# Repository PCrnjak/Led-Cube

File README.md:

# **Led-Cube**

## Intro

Small and compact led cube powered by usb  that is (kinda) easy to build.I decided to make this project for my own amusement and to train smd soldering and pcb design. Code and program are not made  by me all credit goes to: http://www.instructables.com/id/LED-CUBE-CODE-4x4x4-Arduino/ .

## Table of contents
 1. [Intro](#intro)
 2. [Table of contents](#table)
 3. [Bill of materials](#bill)
 4. [Making boards](#board)
 5. [Soldering components](#solder)
 6. [Burning Arduino bootloader](#burn)
 7. [Code](#code)
 8. [Case](#case)

## Bill of materials
  [ Bill of materials](https://github.com/Ropecar5/Led-Cube/blob/master/BILL%20OF%20MATERIALS.txt)
# Making boards
in [GBRLS](https://github.com/Ropecar5/Led-Cube/tree/master/GRBLS) folder there are all grbl files needed to make boards for led cube.
you will need to make 2 boards ,one top one on wich you will place your led cube and one bottom one that has all electronics.
There are also Eagle schematic and board files for both pcbs . I ordered them [JLC pcb](https://jlcpcb.com/) and they came fine.

# Soldering components
 Well you will need to have some skills with soldering iron and solder all those smd components. Hardest part is soldering leds .You will need to cut 16 3mm holes that are 1.5 mm one from another on peace of cardboard. This will keep all leds at exact distance and make soldering easier.you will need to solder all 4 led planes with magnet wire to pcb board.
 
 # Burning Arduino bootlaoder
 Maybe you can find those smd atmega 328 with already burnt bootloader or you can burn it yourself. I made a mistake on board and didnt want to redo it so to burn bootloader follow these instructions.
 solder wires like shown in picture ,  and connect them to ftdi programmer .
Miso to miso , mosi to mosi , sck to sck , gnd to gnd ,vcc to vcc,DTR ON LED BOARD is not dtr .
Connect dtr from ftdi programmer to wire that is shown on picture.Cap on picture is 47 uF.

# Code
Once again code is not written by me. There are 2 example programs [LEDFADE](https://github.com/Ropecar5/Led-Cube/tree/master/LEDFADE) and
[shooting star](https://github.com/Ropecar5/Led-Cube/tree/master/shooting_star).[LCCG.exe](https://github.com/Ropecar5/Led-Cube/blob/master/LCCG.exe) is program used to generate patterns in wich cube will light up.  To upload code you will need FTDI usb to TTL serial converter that connects to corresponding pins on board.
# Case
[STL](https://github.com/Ropecar5/Led-Cube/tree/master/files) file. Printed on cheap chinese prusa clone with 0.2 mm layer height.

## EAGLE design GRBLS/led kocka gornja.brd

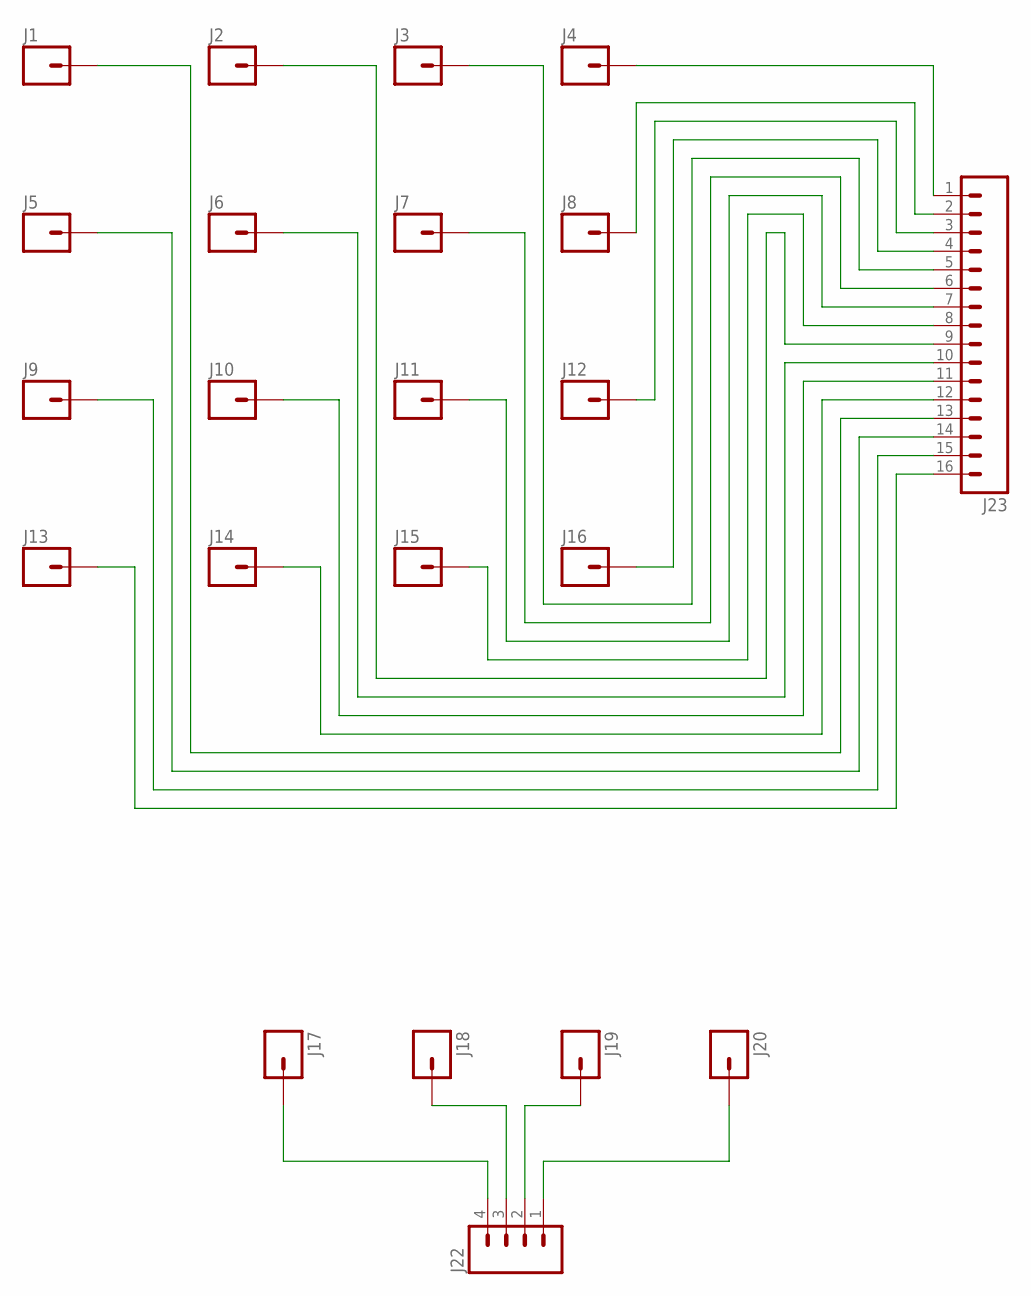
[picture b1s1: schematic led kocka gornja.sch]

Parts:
J1, J2, J3, J4, J5, J6, J7, J8, J9, J10, J11, J12, J13, J14, J15, J16, J17, J18, J19, J20: M01NOSILK-KIT; 1X01NS-KIT
J22: M04LONGPADS; 1X04_LONGPADS
J23: M16LONGPADS; 1X16_LONGPADS

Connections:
unnamed: J4.1, J23.1
unnamed: J8.1, J23.2
unnamed: J12.1, J23.3
unnamed: J16.1, J23.4
unnamed: J3.1, J23.5
unnamed: J7.1, J23.6
unnamed: J11.1, J23.7
unnamed: J15.1, J23.8
unnamed: J2.1, J23.9
unnamed: J6.1, J23.10
unnamed: J14.1, J23.12
unnamed: J1.1, J23.13
unnamed: J10.1, J23.11
unnamed: J5.1, J23.14
unnamed: J9.1, J23.15
unnamed: J13.1, J23.16
unnamed: J17.1, J22.4
unnamed: J20.1, J22.1
unnamed: J18.1, J22.3
unnamed: J19.1, J22.2

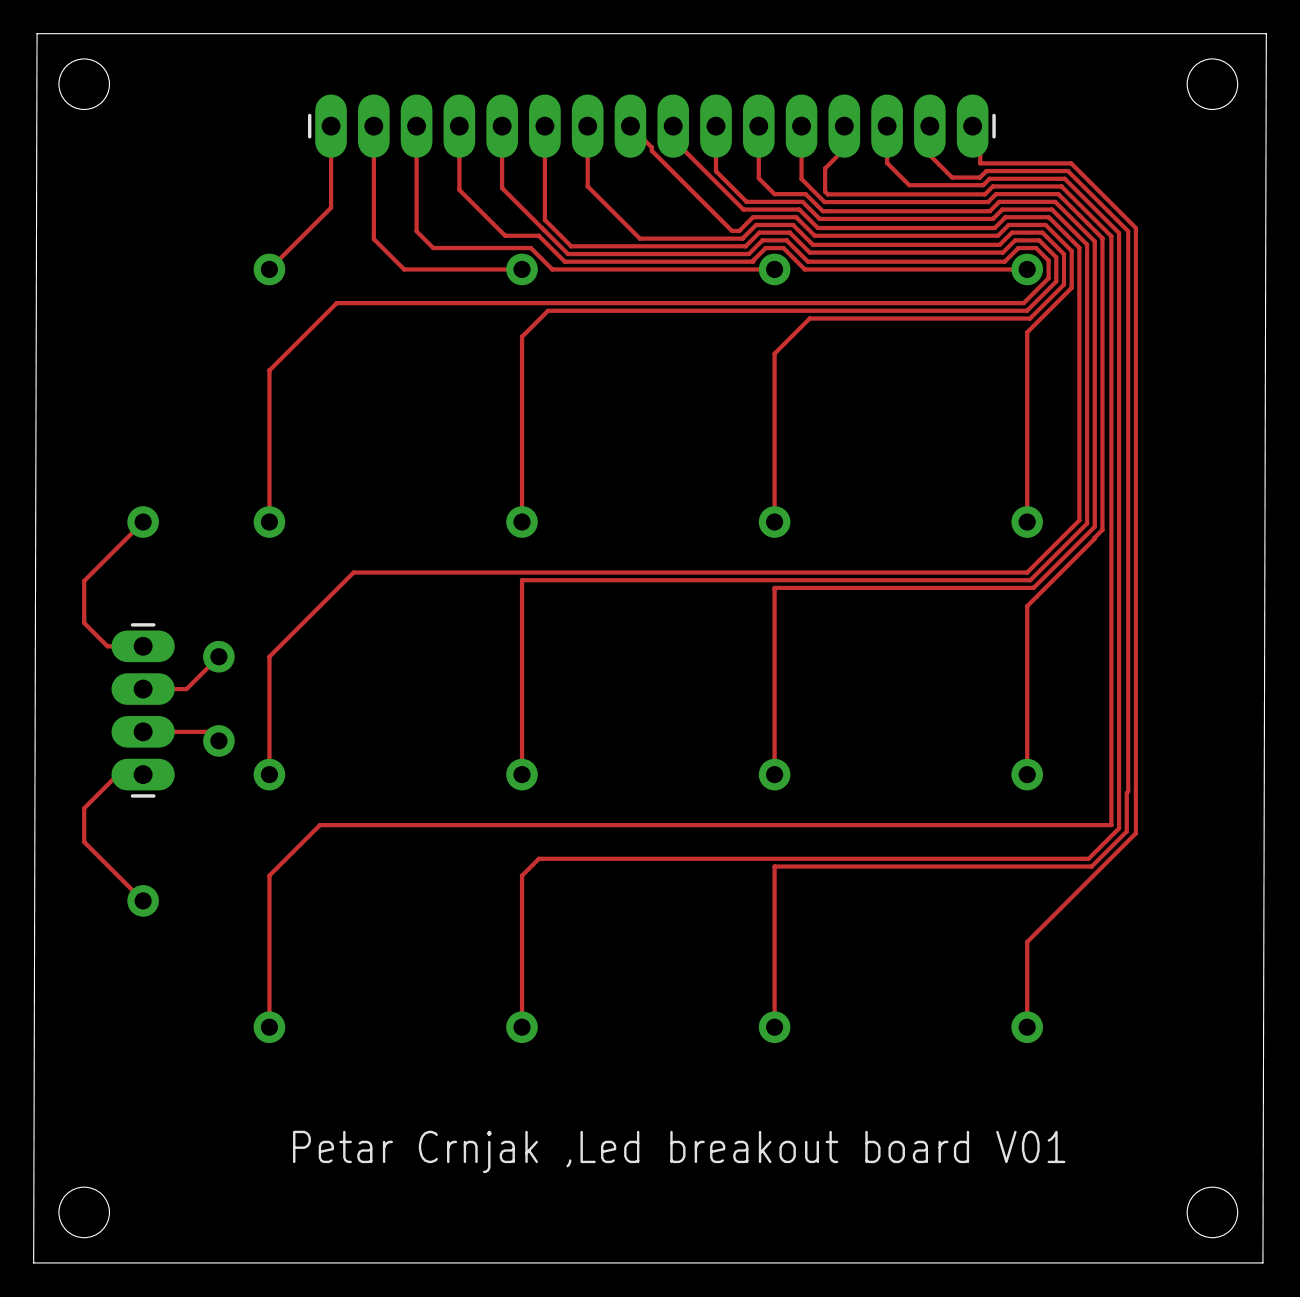
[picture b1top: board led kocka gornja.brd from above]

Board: 2 copper layers, 73.2 x 73.0 mm, 22 parts (0 on the bottom side), 20 nets.

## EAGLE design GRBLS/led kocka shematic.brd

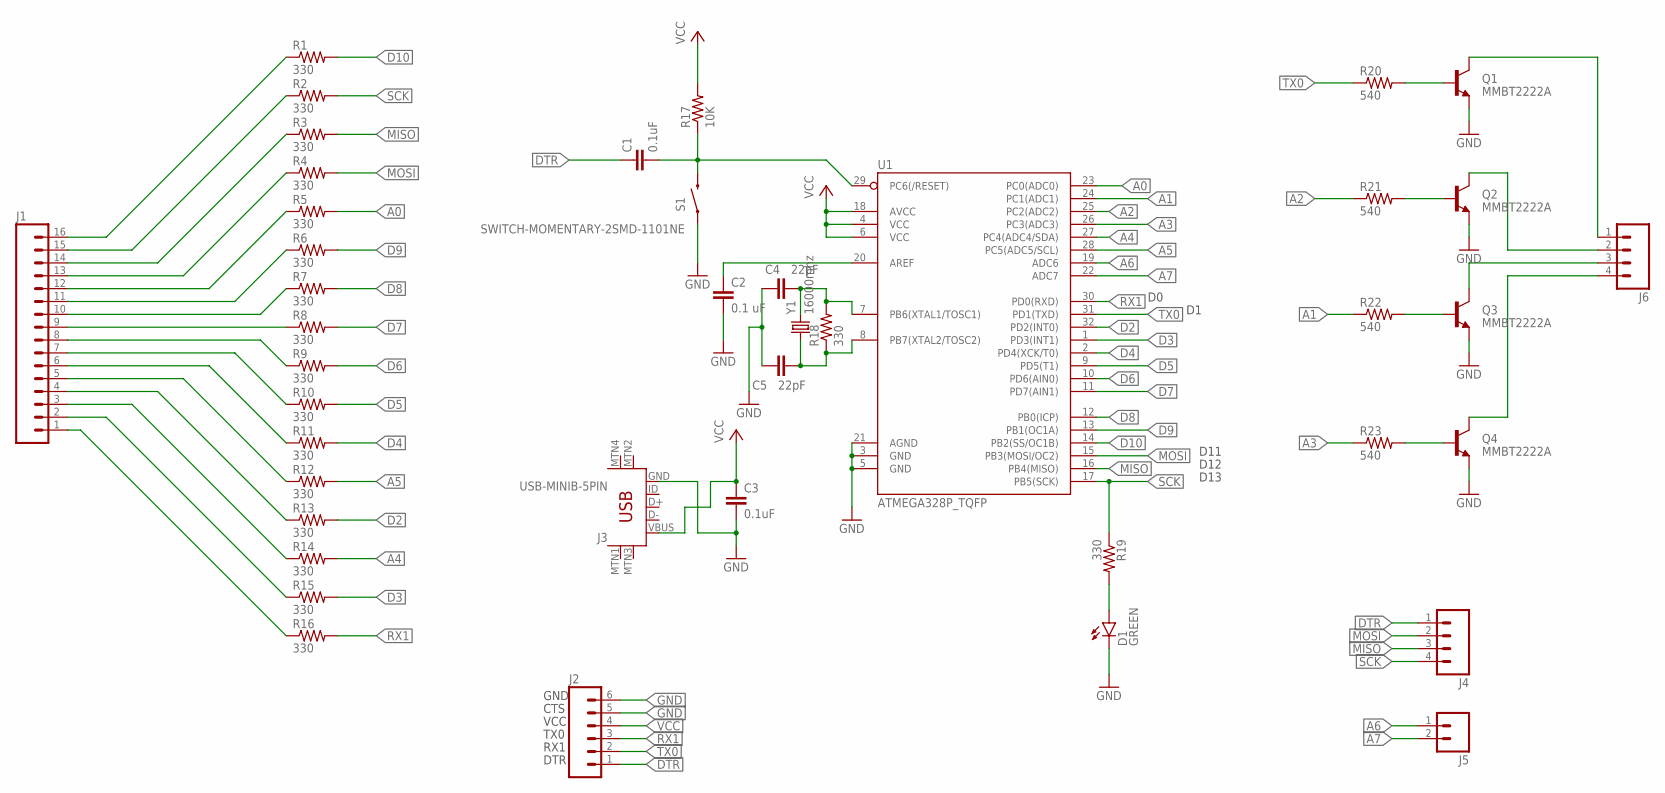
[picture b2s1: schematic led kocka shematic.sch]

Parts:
C1, C3: 0.1uF; 0805-CAP
C2: 0.1 uF; 0805-CAP
C4, C5: 22pF; 0805-CAP
D1: GREEN; LED-0603
J1: M16LONGPADS; 1X16_LONGPADS
J2: M06LONGPADS; 1X06_LONGPADS
J3: USB-MINIB-5PIN; USB-MINIB
J4, J6: M04LONGPADS; 1X04_LONGPADS
J5: M02LOCK_LONGPADS; 1X02_LOCK_LONGPADS
Q1, Q2, Q3, Q4: MMBT2222A; SOT23-3
R1, R2, R3, R4, R5, R6, R7, R8, R9, R10, R11, R12, R13, R14, R15, R16, R18, R19: 330; R0805
R17: 10K; R0805
R20, R21, R22, R23: 540; R0805
S1: SWITCH-MOMENTARY-2SMD-1101NE; TACTILE-SWITCH-1101NE
U1: ATMEGA328P_TQFP; TQFP32-08
Y1: 16000mhz; HC49UP

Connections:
A0: R5.2, U1.23 (PC0(ADC0))
A1: R22.1, U1.24 (PC1(ADC1))
A2: R21.1, U1.25 (PC2(ADC2))
A3: R23.1, U1.26 (PC3(ADC3))
A4: R14.2, U1.27 (PC4(ADC4/SDA))
A5: R12.2, U1.28 (PC5(ADC5/SCL))
A6: J5.1, U1.19 (ADC6)
A7: J5.2, U1.22 (ADC7)
D2: R13.2, U1.32 (PD2(INT0))
D3: R15.2, U1.1 (PD3(INT1))
D4: R11.2, U1.2 (PD4(XCK/T0))
D5: R10.2, U1.9 (PD5(T1))
D6: R9.2, U1.10 (PD6(AIN0))
D7: R8.2, U1.11 (PD7(AIN1))
D8: R7.2, U1.12 (PB0(ICP))
D9: R6.2, U1.13 (PB1(OC1A))
D10: R1.2, U1.14 (PB2(SS/OC1B))
DTR: C1.1, J2.1, J4.1
GND: C2.2, C3.2, C4.1, C5.1, D1.C, J2.5, J2.6, J3.GND, Q1.2 (E), Q2.2 (E), Q3.2 (E), Q4.2 (E), S1.1, U1.3 (GND), U1.5 (GND), U1.21 (AGND)
MISO: J4.3, R3.2, U1.16 (PB4(MISO))
MOSI: J4.2, R4.2, U1.15 (PB3(MOSI/OC2))
unnamed: C4.2, R18.2, U1.7 (PB6(XTAL1/TOSC1)), Y1.2
unnamed: J1.16, R1.1
unnamed: C1.2, R17.1, S1.2, U1.29 (PC6(/RESET))
unnamed: C5.2, R18.1, U1.8 (PB7(XTAL2/TOSC2)), Y1.1
unnamed: C2.1, U1.20 (AREF)
unnamed: J1.15, R2.1
unnamed: J1.14, R3.1
unnamed: J1.13, R4.1
unnamed: J1.12, R5.1
unnamed: J1.11, R6.1
unnamed: D1.A, R19.2
unnamed: J1.1, R16.1
unnamed: J1.2, R15.1
unnamed: J1.3, R14.1
unnamed: J1.4, R13.1
unnamed: J1.5, R12.1
unnamed: J1.6, R11.1
unnamed: J1.7, R10.1
unnamed: J1.8, R9.1
unnamed: J1.9, R8.1
unnamed: J1.10, R7.1
unnamed: Q1.1 (B), R20.2
unnamed: Q2.1 (B), R21.2
unnamed: Q3.1 (B), R22.2
unnamed: Q4.1 (B), R23.2
unnamed: J6.1, Q1.3 (C)
unnamed: J6.2, Q2.3 (C)
unnamed: J6.3, Q3.3 (C)
unnamed: J6.4, Q4.3 (C)
RX1: J2.3, R16.2, U1.30 (PD0(RXD))
SCK: J4.4, R2.2, R19.1, U1.17 (PB5(SCK))
TX0: J2.2, R20.1, U1.31 (PD1(TXD))
VCC: C3.1, J2.4, J3.VBUS, R17.2, U1.4 (VCC), U1.6 (VCC), U1.18 (AVCC)

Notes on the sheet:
GND
CTS
VCC
TX0
RX1
DTR
D13
D12
D11

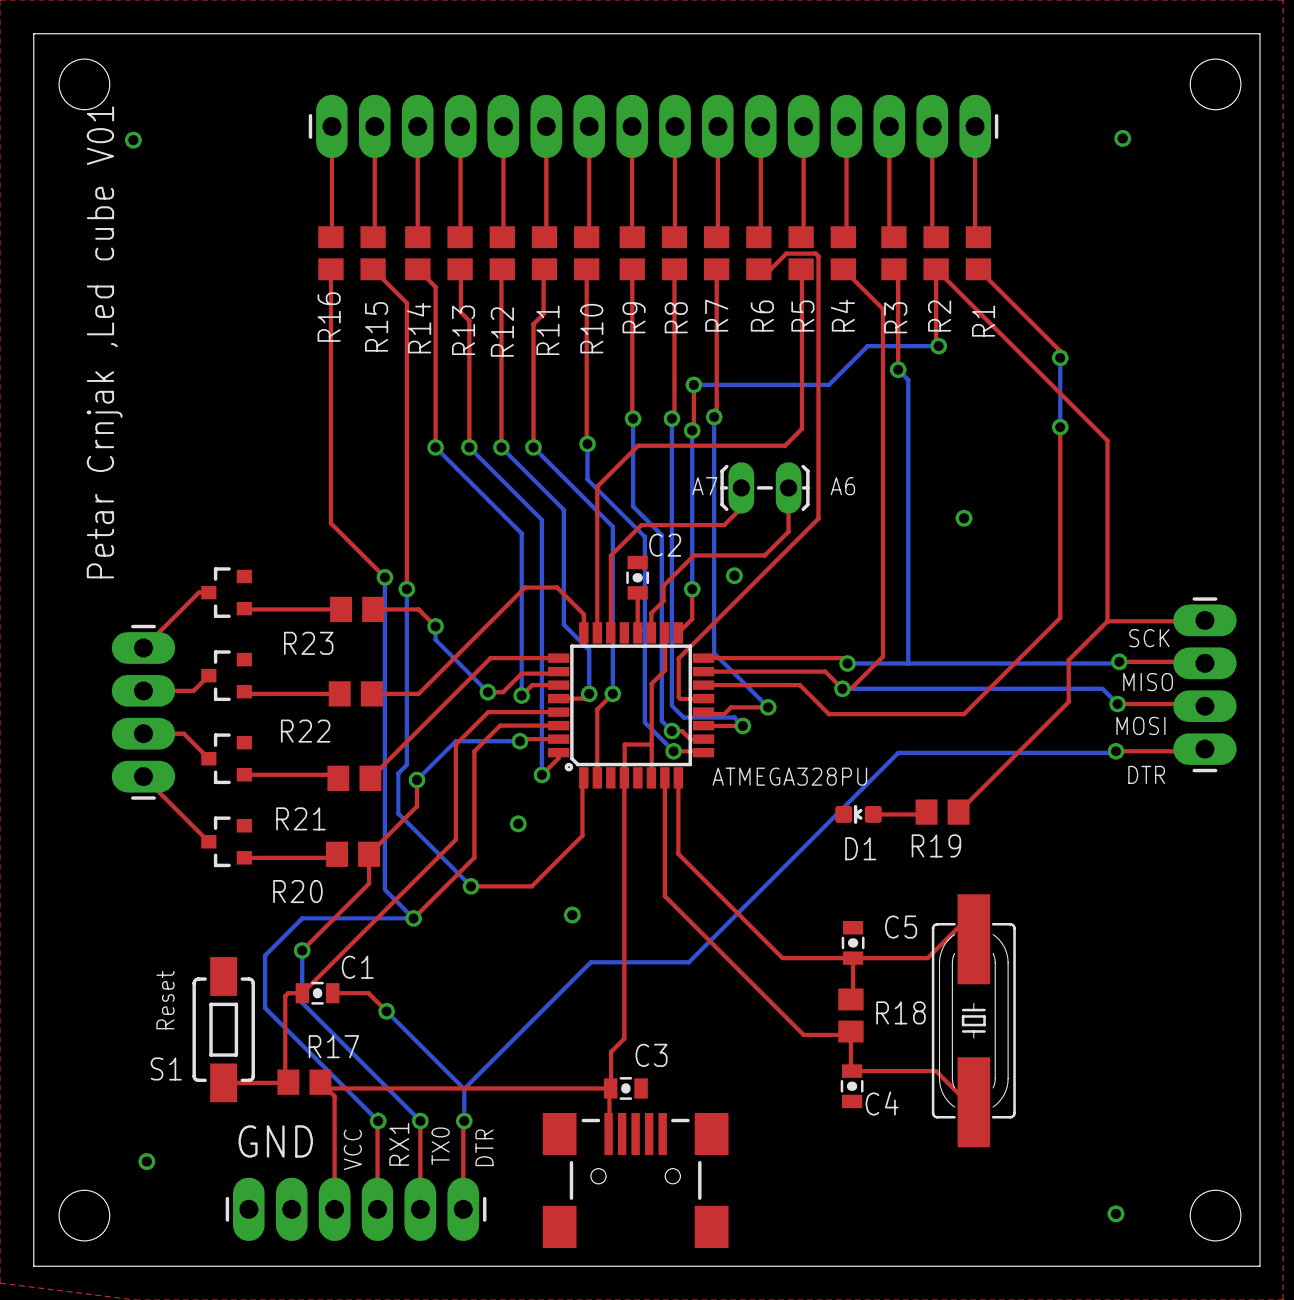
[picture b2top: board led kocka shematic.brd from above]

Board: 2 copper layers, 72.6 x 73.0 mm, 42 parts (0 on the bottom side), 54 nets.

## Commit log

2018-04-03 Create how to upload bootloader
2018-07-30 a
    dasdsd

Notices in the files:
parts and their libraries:
SparkFun-Connectors: Licensing: Creative Commons ShareAlike 4.0 International - https://creativecommons.org/licenses/by-sa/4.0
